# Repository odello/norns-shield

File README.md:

# norns-shield

minimal/tiny open-source/DIY shield for Raspberry Pi boards, providing hardware compatibility with the [norns](https://monome.org) ecosystem.

- audio codec: CS4270
- audio jacks: 3.5mm stereo in/out, line level
- OLED: NHD-2.7-12864WDW3
- 3x pushbuttons, 3x rotary encoders

see the full [BOM on Octopart](https://octopart.com/bom-tool/Q3rQej3x)

see [https://llllllll.co/t/diy-norns-shield](https://llllllll.co/t/diy-norns-shield/27638) for discussion.

[monome.org](https://monome.org)

full kit available from [monome.org](https://market.monome.org)

## assembly

for SMD-populated circuit.

parts shown (header already soldered to OLED)

first solder the OLED header (make sure the orientation looks like the photo below, as we've had a few reports of folks placing their headers on the wrong side). then the encoders, and keys.

then attach the pi header to the other side and solder as shown.

attach the screen to the top. note that you may have to apply substantial pressure for it to connect: put something hard on top of the header while applying pressure so you don't wreck your thumbs.

likewise, attaching the keycaps requires substantial pressure. be sure they are aligned well then press hard.

the knobs should go on easily in comparison.

---

attach the shortest spacers with short screws, which props up the screen.

four spacers with the male thread insert from the top. for the bottom, the long remaining spacers go in front, shorter in back as shown.

align the plate and attach with short screws. don't tighten the screws until you've aligned the keys and knobs, as there's a little wiggle room for fine tuning.

attach the pi and add two plastic spacers, then balance the plate on top. the holes with spacers need the two long screws, the front use short screws.

## setting up

get [the latest shield image from github](https://github.com/monome/norns-image/releases).

use [etcher](https://www.balena.io/etcher/) to make your SD card. it's by far the most reliable method.

## troubleshooting

- most soldering problems can be solved simply by reheating solder joints. bad solders can result in various problems: screen doesn't turn on, knobs/keys don't work.
- use a good SD card, not a cheap one. if you're having trouble, try using a different card.
- be sure to use the correct power supply. the pi will not power well from a laptop and you'll get confusing errors. get a dedicated 2A USB supply, or very high output USB battery.

if your SD card seems a lot more full than it should be, you'll need to expand the filesystem:
- open a terminal on a computer connected to the same network as your shield
- execute: `ssh we@norns.local`
- password: `sleep`
- execute: `sudo raspi-config`
- navigate to `Advanced` and hit RETURN
- select `expand filesystem` and hit RETURN
- lots of activity will happen. when it's done, power down and reboot. if you get any errors, reboot again.
- if you SSH back into norns and execute `df -h`, you'll see the newly expanded capacity.

## notes

- the shield does not have a headphone output, but headphones work fine on the main output. the headphone gain level within the norns menu does nothing in this case.
- the battery indication will not function, as there's no battery.

## mechanicals

- 2 Female Threaded Hex Standoff Aluminum, 3/16" Hex, 5/16" Long, 2-56 Thread 91780A104
- 2 Female Threaded Hex Standoff Aluminum, 3/16" Hex, 5/8" Long, 2-56 Thread 91780A111
- 2 Female Threaded Hex Standoff Aluminum, 3/16" Hex, 3/4" Long, 2-56 Thread 91780A113
- 4 Male-Female Threaded Hex Standoff Aluminum, 3/16" Hex Size, 1/2" Long, 2-56 Thread Size 93505A213
- 4 Off-White Nylon Unthreaded Spacer 1/4" OD, 3/32" Long, for Number 6 Screw Size 94639A247
- 8 Black-Oxide 18-8 Stainless Steel Pan Head Phillips Screws 2-56 Thread, 1/4" Long 91249A050
- 2 Black-Oxide 18-8 Stainless Steel Pan Head Phillips Screws 2-56 Thread, 3/8" Long 91249A054

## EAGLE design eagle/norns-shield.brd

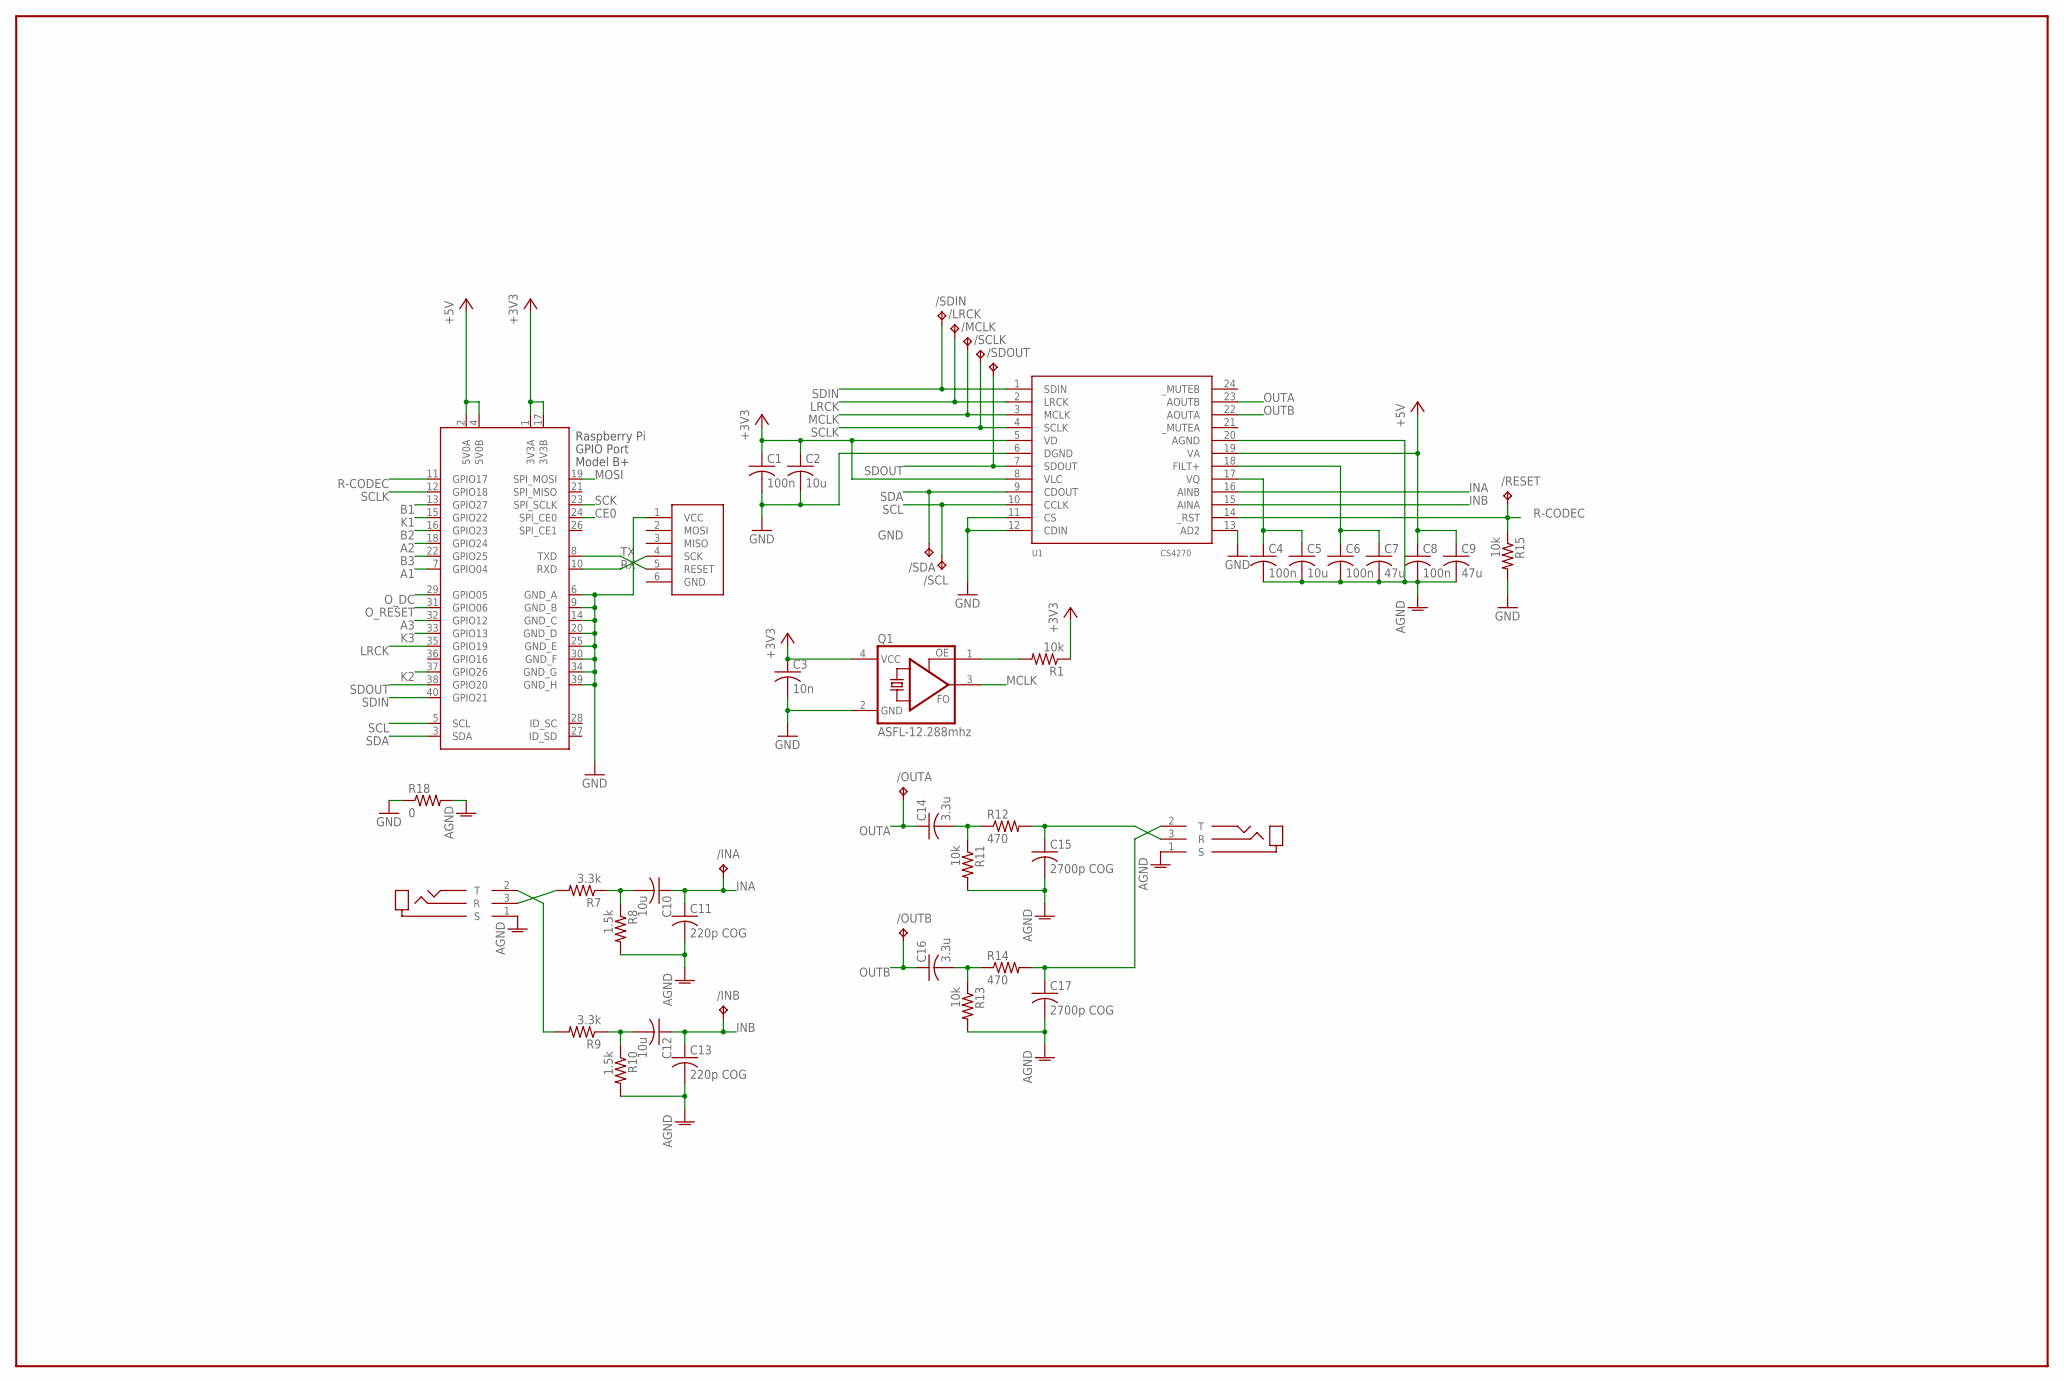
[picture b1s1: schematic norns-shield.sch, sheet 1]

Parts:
/INA: TPTP12R; TP12R
/INB: TPTP12R; TP12R
/LRCK: TPTP12R; TP12R
/MCLK: TPTP12R; TP12R
/OUTA: TPTP12R; TP12R
/OUTB: TPTP12R; TP12R
/RESET: TPTP12R; TP12R
/SCL: TPTP12R; TP12R
/SCLK: TPTP12R; TP12R
/SDA: TPTP12R; TP12R
/SDIN: TPTP12R; TP12R
/SDOUT: TPTP12R; TP12R
C1, C4, C6, C8: 100n; C0603
C2, C5, C10, C12: 10u; C0805
C3: 10n; C0603
C7, C9: 47u; C1206
C11, C13: 220p COG; C0603
C14, C16: 3.3u; C0805
C15, C17: 2700p COG; C0603
J1: TRS-IN; SJ-3523-SMT
J2: TRS-OUT; SJ-3523-SMT
J3: ISP-ROW
Q1: ASFL-12.288mhz; ASF
R1, R11, R13, R15: 10k; R0603
R7, R9: 3.3k; R0603
R8, R10: 1.5k; R0603
R12, R14: 470; R0603
R18: 0; R0603
U1: CS4270; TSSOP24
X1: RASPI_BOARD_B+#_E3; RASPI_BOARD_B+_EDGES_3DRILL

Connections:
+3V3: C1.1, C2.1, C3.1, Q1.4 (VCC), R1.1, U1.5 (VD), U1.8 (VLC), X1.1 (3V3A), X1.17 (3V3B); also elsewhere on the board
+5V: C8.1, C9.1, U1.19 (VA), X1.2 (5V0A), X1.4 (5V0B)
A1: X1.7 (GPIO04); also elsewhere on the board
A2: X1.18 (GPIO24); also elsewhere on the board
A3: X1.32 (GPIO12); also elsewhere on the board
AGND: C4.2, C5.2, C6.2, C7.2, C8.2, C9.2, C11.2, C13.2, C15.2, C17.2, J1.1 (S), J2.1 (S), R8.2, R10.2, R11.2, R13.2, R18.2, U1.20 (AGND)
B1: X1.13 (GPIO27); also elsewhere on the board
B2: X1.16 (GPIO23); also elsewhere on the board
B3: X1.22 (GPIO25); also elsewhere on the board
CE0: X1.24 (SPI_CE0); also elsewhere on the board
GND: C1.2, C2.2, C3.2, J3.1 (VCC), Q1.2 (GND), R15.2, R18.1, U1.6 (DGND), U1.11 (CS), U1.12 (CDIN), U1.13 (AD2), X1.6 (GND_A), X1.9 (GND_B), X1.14 (GND_C), X1.20 (GND_D), X1.25 (GND_E), X1.30 (GND_F), X1.34 (GND_G), X1.39 (GND_H); also elsewhere on the board
INA: /INA.TP, C10.1, C11.1, U1.16 (AINB)
INB: /INB.TP, C12.1, C13.1, U1.15 (AINA)
K1: X1.15 (GPIO22); also elsewhere on the board
K2: X1.37 (GPIO26); also elsewhere on the board
K3: X1.33 (GPIO13); also elsewhere on the board
LRCK: /LRCK.TP, U1.2 (LRCK), X1.35 (GPIO19)
MCLK: /MCLK.TP, Q1.3 (FO), U1.3 (MCLK)
MOSI: X1.19 (SPI_MOSI); also elsewhere on the board
unnamed: Q1.1 (OE), R1.2
unnamed: C4.1, C5.1, U1.17 (VQ)
unnamed: C6.1, C7.1, U1.18 (FILT+)
unnamed: J1.3 (R), R7.2
unnamed: C10.2, R7.1, R8.1
unnamed: C12.2, R9.1, R10.1
unnamed: J1.2 (T), R9.2
unnamed: C16.2, R13.1, R14.1
unnamed: C14.2, R11.1, R12.1
unnamed: C15.1, J2.3 (R), R12.2
unnamed: C17.1, J2.2 (T), R14.2
OUTA: /OUTA.TP, C14.1, U1.23 (AOUTB)
OUTB: /OUTB.TP, C16.1, U1.22 (AOUTA)
O_DC: X1.29 (GPIO05); also elsewhere on the board
O_RESET: X1.31 (GPIO06); also elsewhere on the board
R-CODEC: /RESET.TP, R15.1, U1.14 (_RST), X1.11 (GPIO17)
RX: J3.4 (SCK), X1.10 (RXD)
SCK: X1.23 (SPI_SCLK); also elsewhere on the board
SCL: /SCL.TP, U1.10 (CCLK), X1.5 (SCL)
SCLK: /SCLK.TP, U1.4 (SCLK), X1.12 (GPIO18)
SDA: /SDA.TP, U1.9 (CDOUT), X1.3 (SDA)
SDIN: /SDIN.TP, U1.1 (SDIN), X1.40 (GPIO21)
SDOUT: /SDOUT.TP, U1.7 (SDOUT), X1.38 (GPIO20)
TX: J3.5 (RESET), X1.8 (TXD)

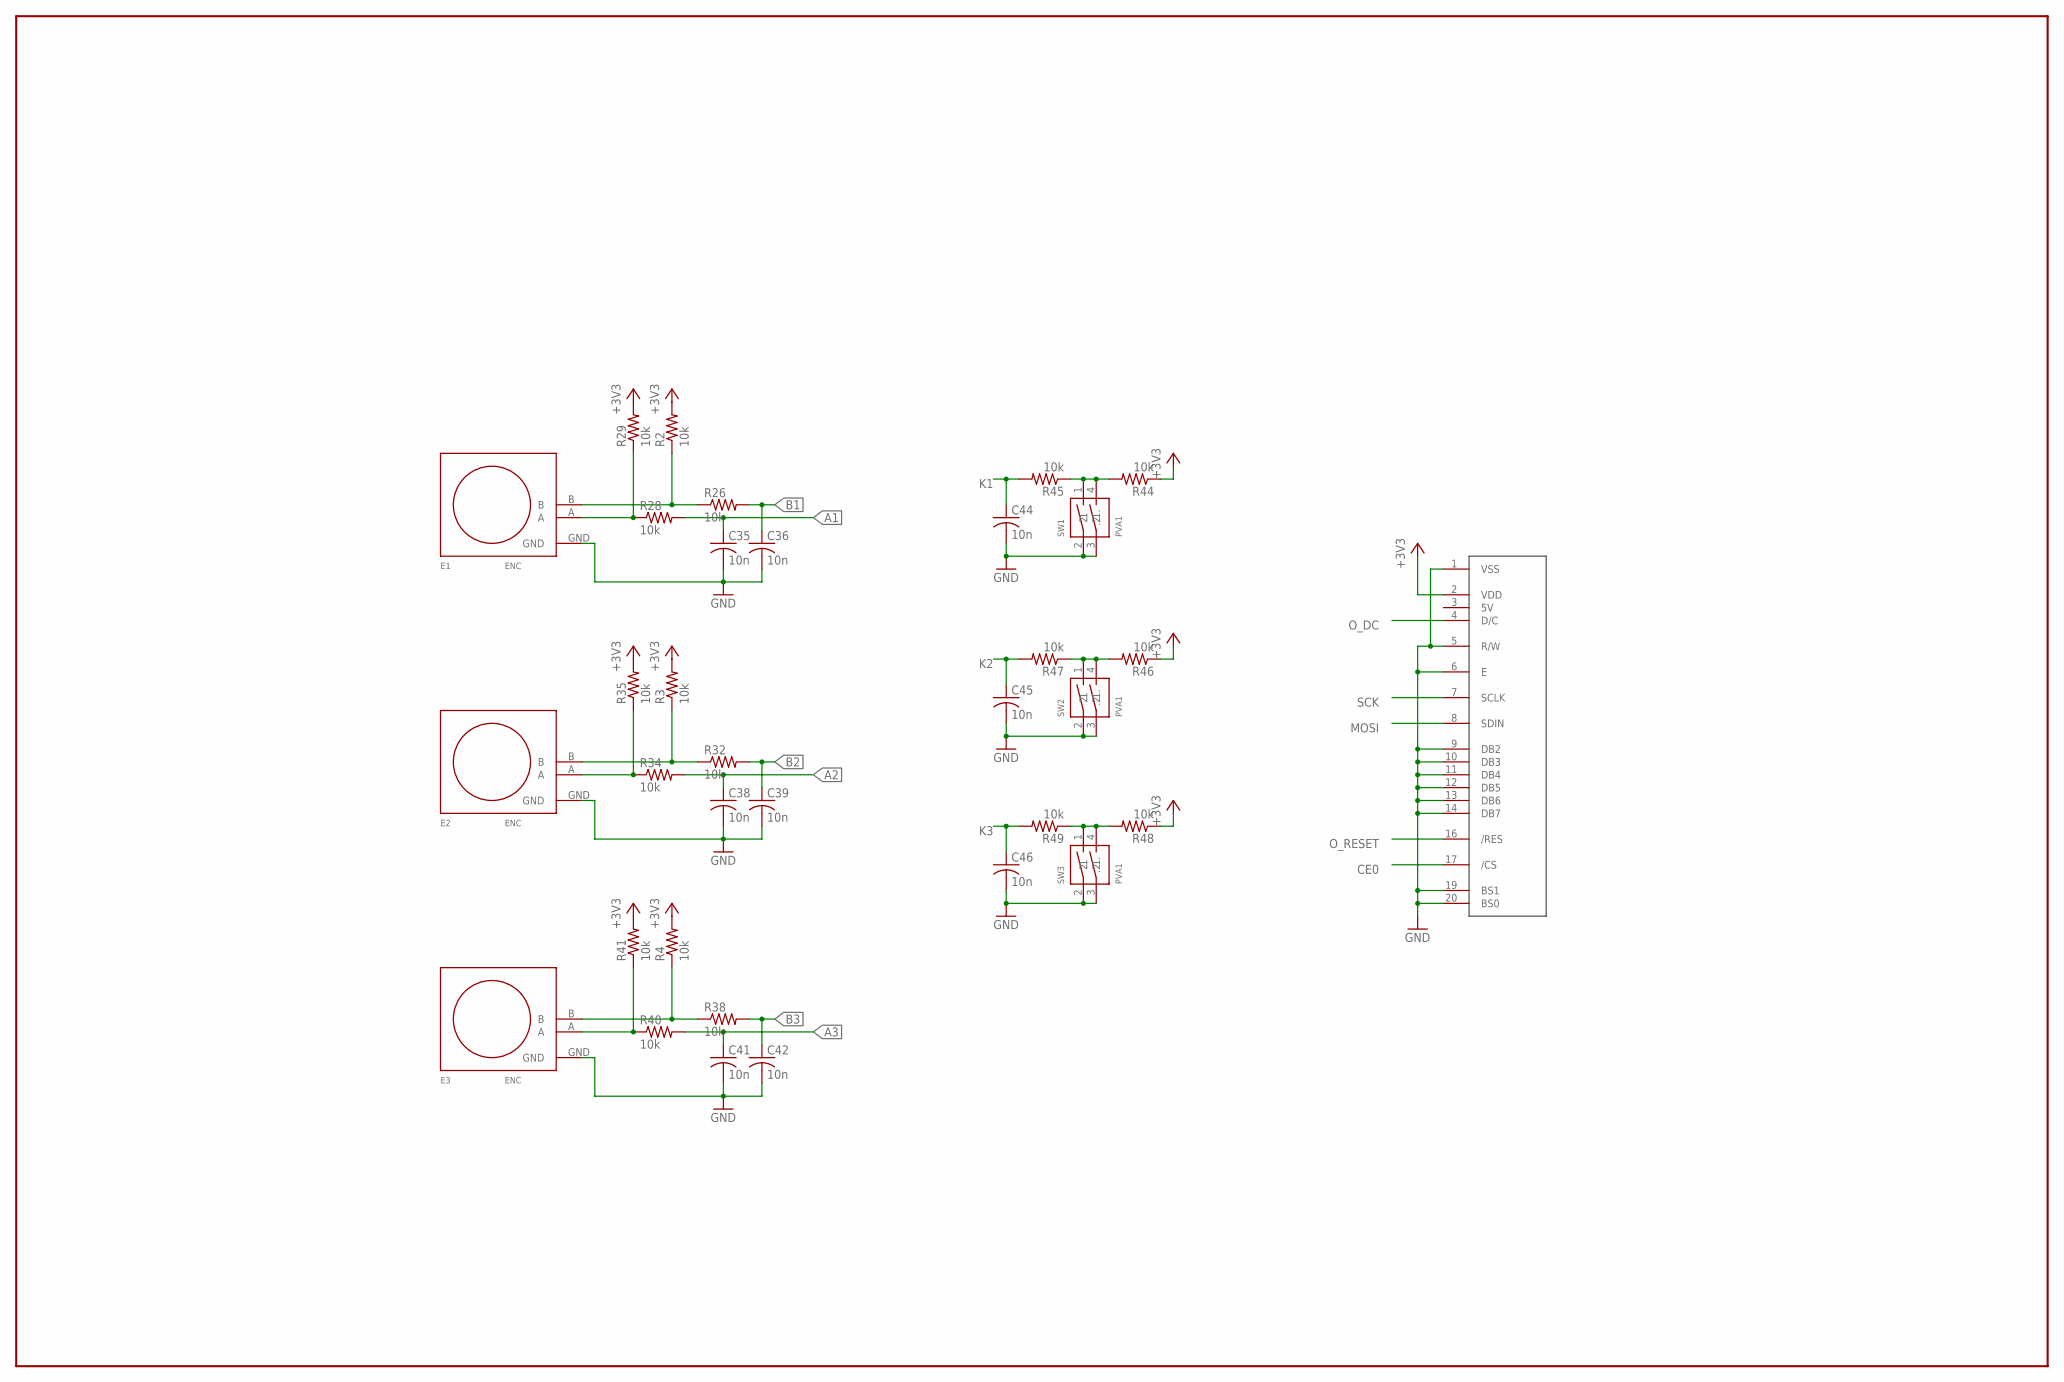
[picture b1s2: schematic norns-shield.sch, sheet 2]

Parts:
C35, C36, C38, C39, C41, C42, C44, C45, C46: 10n; C0603
E1, E2, E3: ENC; PEC11RN
R2, R3, R4, R26, R28, R29, R32, R34, R35, R38, R40, R41, R44, R45, R46, R47, R48, R49: 10k; R0603
SW1, SW2, SW3: PVA1
U$1: OLED128X64; OLED-ALEPH

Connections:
+3V3: R2.2, R3.2, R4.2, R29.2, R35.2, R41.2, R44.1, R46.1, R48.1, U$1.2 (VDD); also elsewhere on the board
A1: C35.1, R28.2; also elsewhere on the board
A2: C38.1, R34.2; also elsewhere on the board
A3: C41.1, R40.2; also elsewhere on the board
B1: C36.1, R26.2; also elsewhere on the board
B2: C39.1, R32.2; also elsewhere on the board
B3: C42.1, R38.2; also elsewhere on the board
CE0: U$1.17 (/CS); also elsewhere on the board
GND: C35.2, C36.2, C38.2, C39.2, C41.2, C42.2, C44.2, C45.2, C46.2, E1.GND, E2.GND, E3.GND, SW1.2 (1), SW1.3 (1.), SW2.2 (1), SW2.3 (1.), SW3.2 (1), SW3.3 (1.), U$1.1 (VSS), U$1.5 (R/W), U$1.6 (E), U$1.9 (DB2), U$1.10 (DB3), U$1.11 (DB4), U$1.12 (DB5), U$1.13 (DB6), U$1.14 (DB7), U$1.19 (BS1), U$1.20 (BS0); also elsewhere on the board
K1: C44.1, R45.2; also elsewhere on the board
K2: C45.1, R47.2; also elsewhere on the board
K3: C46.1, R49.2; also elsewhere on the board
MOSI: U$1.8 (SDIN); also elsewhere on the board
unnamed: R44.2, R45.1, SW1.1 (2), SW1.4 (.2)
unnamed: R46.2, R47.1, SW2.1 (2), SW2.4 (.2)
unnamed: R48.2, R49.1, SW3.1 (2), SW3.4 (.2)
unnamed: E1.A, R28.1, R29.1
unnamed: E1.B, R2.1, R26.1
unnamed: E2.B, R3.1, R32.1
unnamed: E2.A, R34.1, R35.1
unnamed: E3.B, R4.1, R38.1
unnamed: E3.A, R40.1, R41.1
O_DC: U$1.4 (D/C); also elsewhere on the board
O_RESET: U$1.16 (/RES); also elsewhere on the board
SCK: U$1.7 (SCLK); also elsewhere on the board

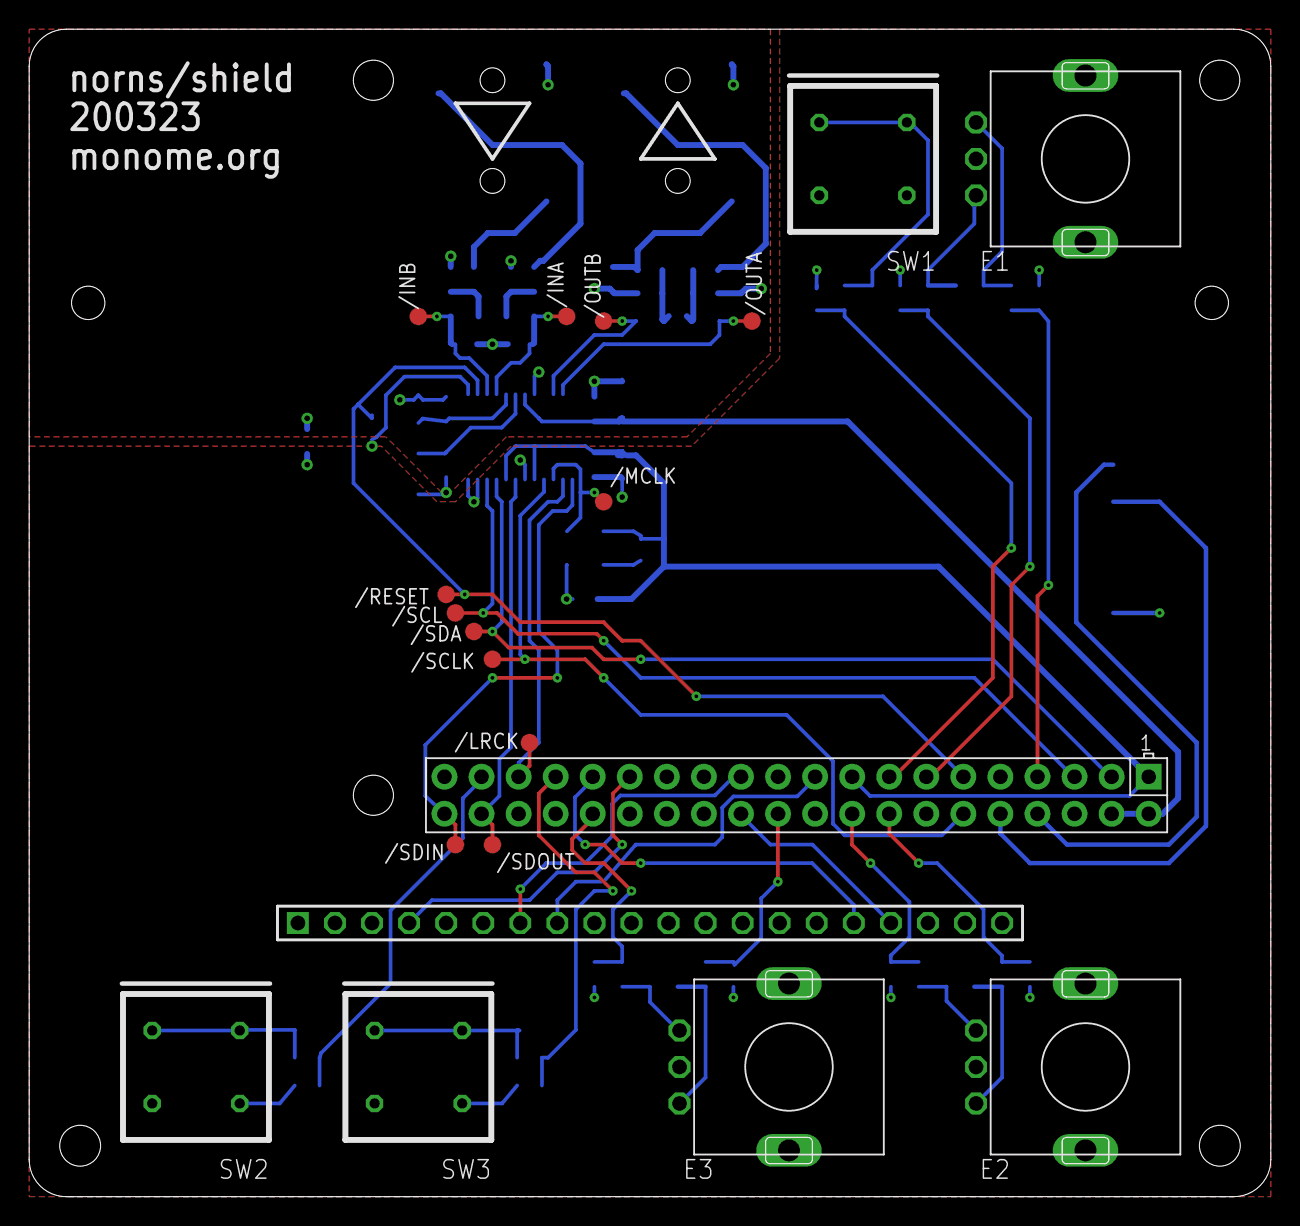
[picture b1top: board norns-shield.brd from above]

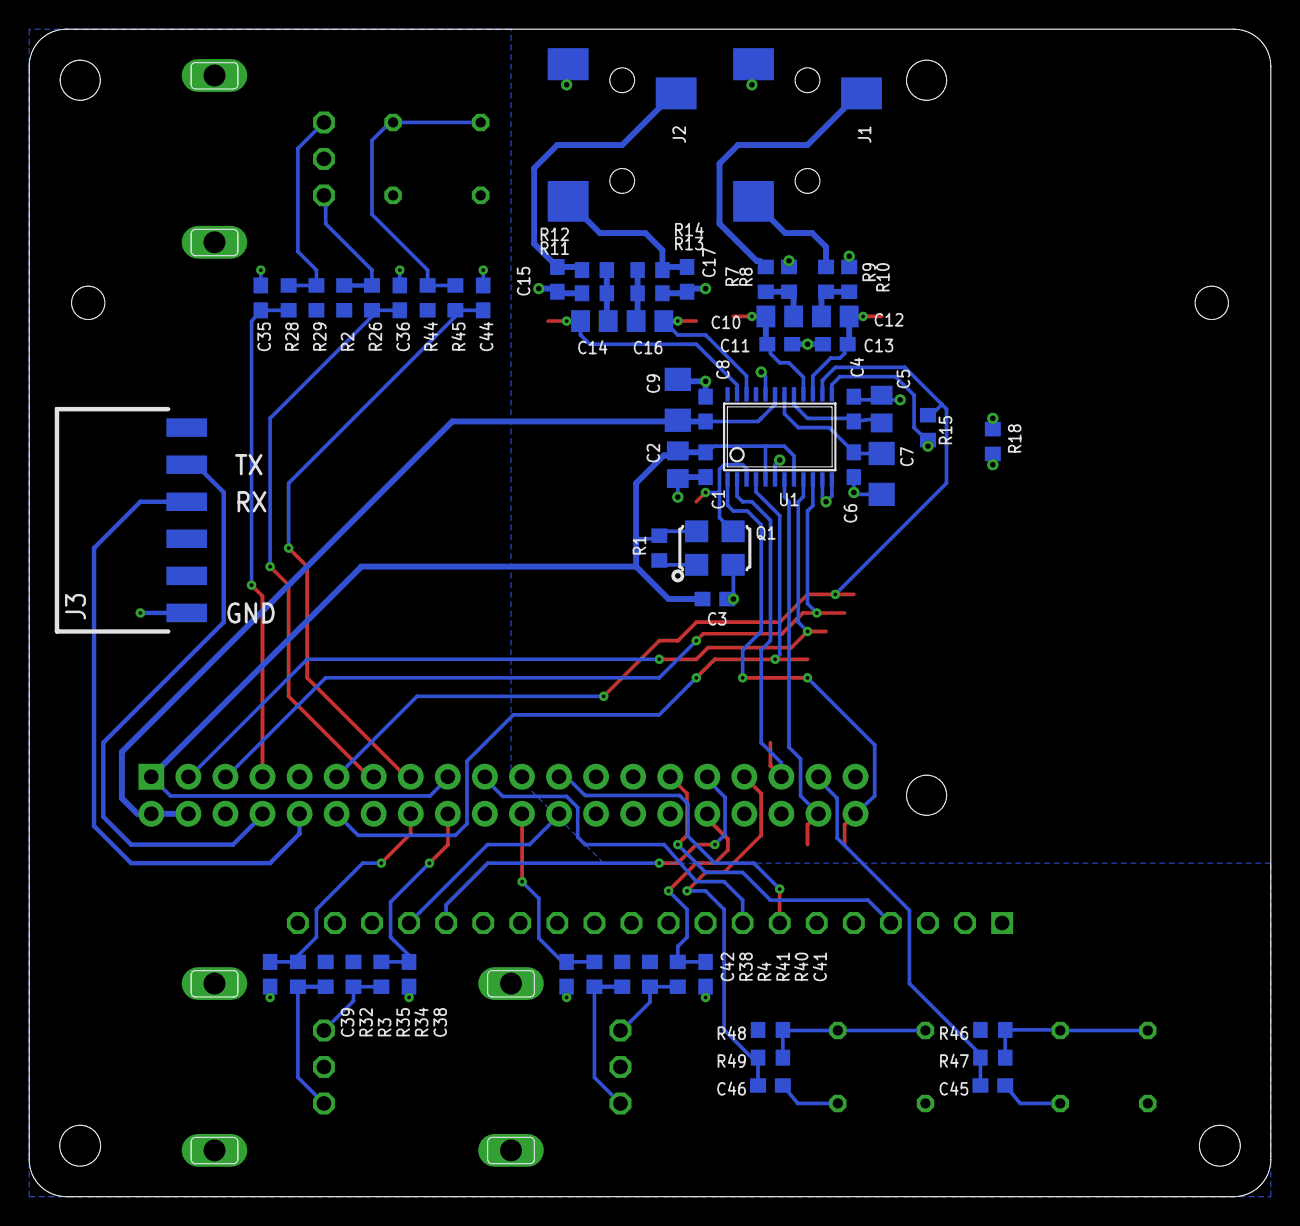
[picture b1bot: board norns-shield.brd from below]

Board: 2 copper layers, 85.1 x 80.0 mm, 80 parts (60 on the bottom side), 52 nets.

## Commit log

2022-02-22 case stl
2022-05-02 Update README.md
    Changed link to norns image
